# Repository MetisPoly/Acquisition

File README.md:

# Acquisition

Voici le _repository_ pour l'équipe d'acquisition des données. Vous trouverez ici les divers codes et schémas de PCB associés à l'équipe.

Si vous n'êtes pas familier avec l'utilisation de _GitHub_, référez-vous à la documentation suivante:
https://docs.google.com/document/d/1EO_ZASFU5IuZBYXzvok4T1j8fdGlCsaUoXh5eMMK4JE/edit?usp=sharing

Si vous voulez apporter des modifications au code existant dans ce _repo_, vous devez impérativement faire un _pull request_. 
Prenez également garde aux branches sur lesquelles vous développez.

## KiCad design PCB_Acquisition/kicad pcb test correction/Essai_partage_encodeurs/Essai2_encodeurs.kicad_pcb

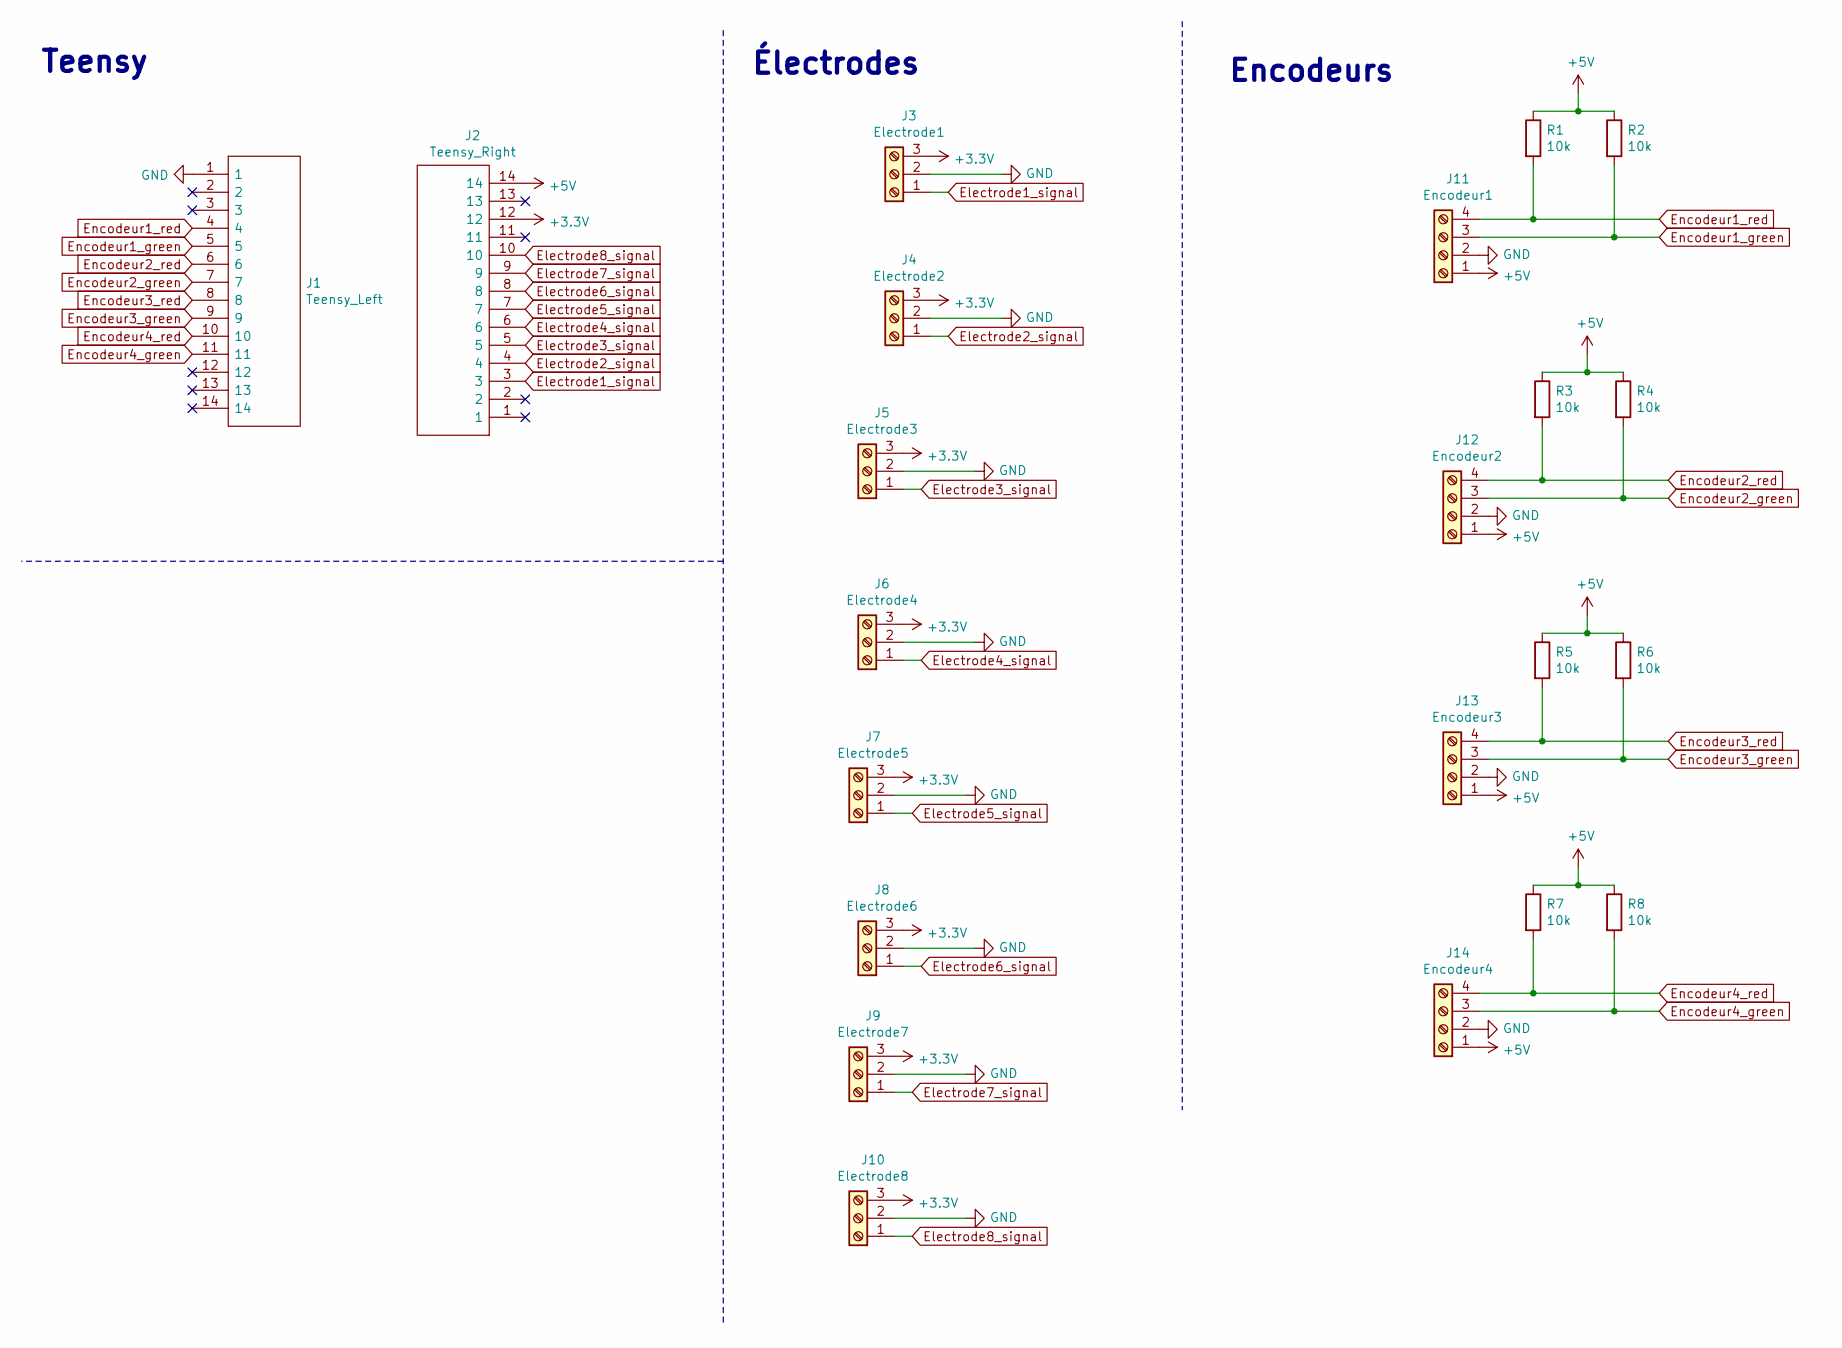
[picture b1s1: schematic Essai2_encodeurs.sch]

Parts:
J1: Teensy_Left; PinSocket_1x14_P2.54mm_Vertical
J2: Teensy_Right; PinSocket_1x14_P2.54mm_Vertical
J3: Electrode1; TerminalBlock_bornier-3_P5.08mm
J4: Electrode2; TerminalBlock_bornier-3_P5.08mm
J5: Electrode3; TerminalBlock_bornier-3_P5.08mm
J6: Electrode4; TerminalBlock_bornier-3_P5.08mm
J7: Electrode5; TerminalBlock_bornier-3_P5.08mm
J8: Electrode6; TerminalBlock_bornier-3_P5.08mm
J9: Electrode7; TerminalBlock_bornier-3_P5.08mm
J10: Electrode8; TerminalBlock_bornier-3_P5.08mm
J11: Encodeur1; TerminalBlock_bornier-4_P5.08mm
J12: Encodeur2; TerminalBlock_bornier-4_P5.08mm
J13: Encodeur3; TerminalBlock_bornier-4_P5.08mm
J14: Encodeur4; TerminalBlock_bornier-4_P5.08mm
R1, R2, R3, R4, R5, R6, R7, R8: 10k; R_0603_1608Metric

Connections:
+3V3: J2.12, J3.3, J4.3, J5.3, J6.3, J7.3, J8.3, J9.3, J10.3
+5V: J2.14, J11.1, J12.1, J13.1, J14.1, R1.1, R2.1, R3.1, R4.1, R5.1, R6.1, R7.1, R8.1
Electrode1_signal: J2.3, J3.1
Electrode2_signal: J2.4, J4.1
Electrode3_signal: J2.5, J5.1
Electrode4_signal: J2.6, J6.1
Electrode5_signal: J2.7, J7.1
Electrode6_signal: J2.8, J8.1
Electrode7_signal: J2.9, J9.1
Electrode8_signal: J2.10, J10.1
Encodeur1_green: J1.5, J11.3, R2.2
Encodeur1_red: J1.4, J11.4, R1.2
Encodeur2_green: J1.7, J12.3, R4.2
Encodeur2_red: J1.6, J12.4, R3.2
Encodeur3_green: J1.9, J13.3, R6.2
Encodeur3_red: J1.8, J13.4, R5.2
Encodeur4_green: J1.11, J14.3, R8.2
Encodeur4_red: J1.10, J14.4, R7.2
GND: J1.1, J3.2, J4.2, J5.2, J6.2, J7.2, J8.2, J9.2, J10.2, J11.2, J12.2, J13.2, J14.2

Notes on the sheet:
Teensy
Électrodes
Encodeurs

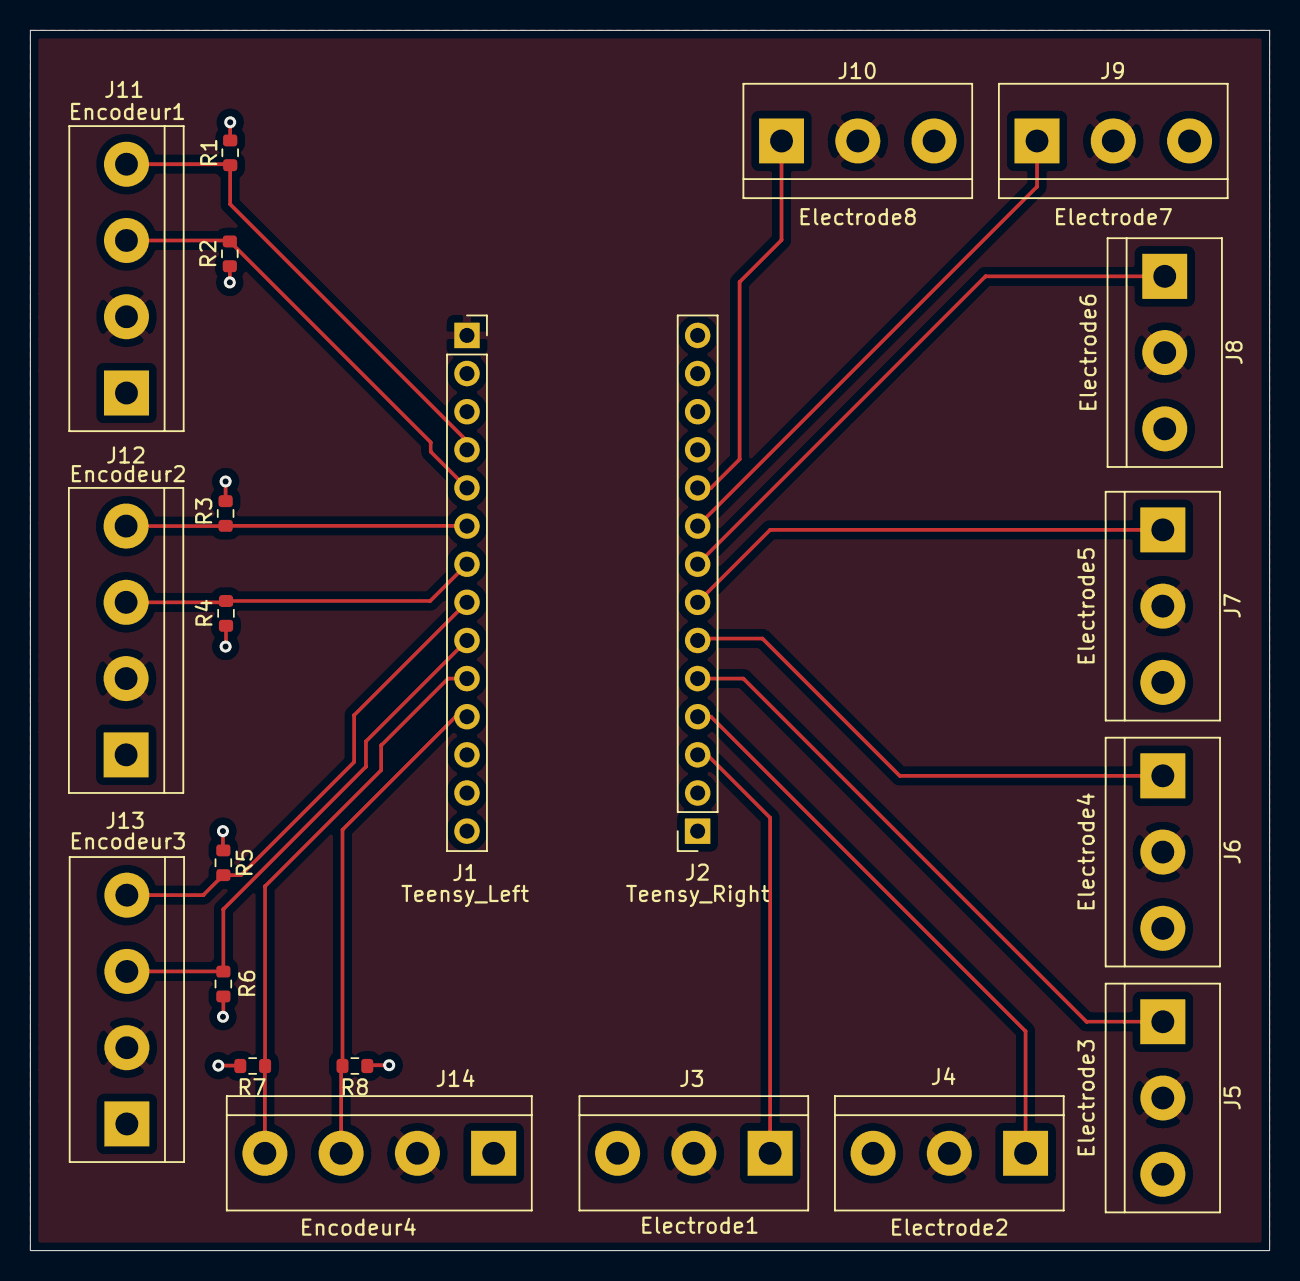
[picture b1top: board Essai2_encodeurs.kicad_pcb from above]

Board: 4 copper layers, 82.5 x 81.3 mm, 22 parts (0 on the bottom side), 19 nets.

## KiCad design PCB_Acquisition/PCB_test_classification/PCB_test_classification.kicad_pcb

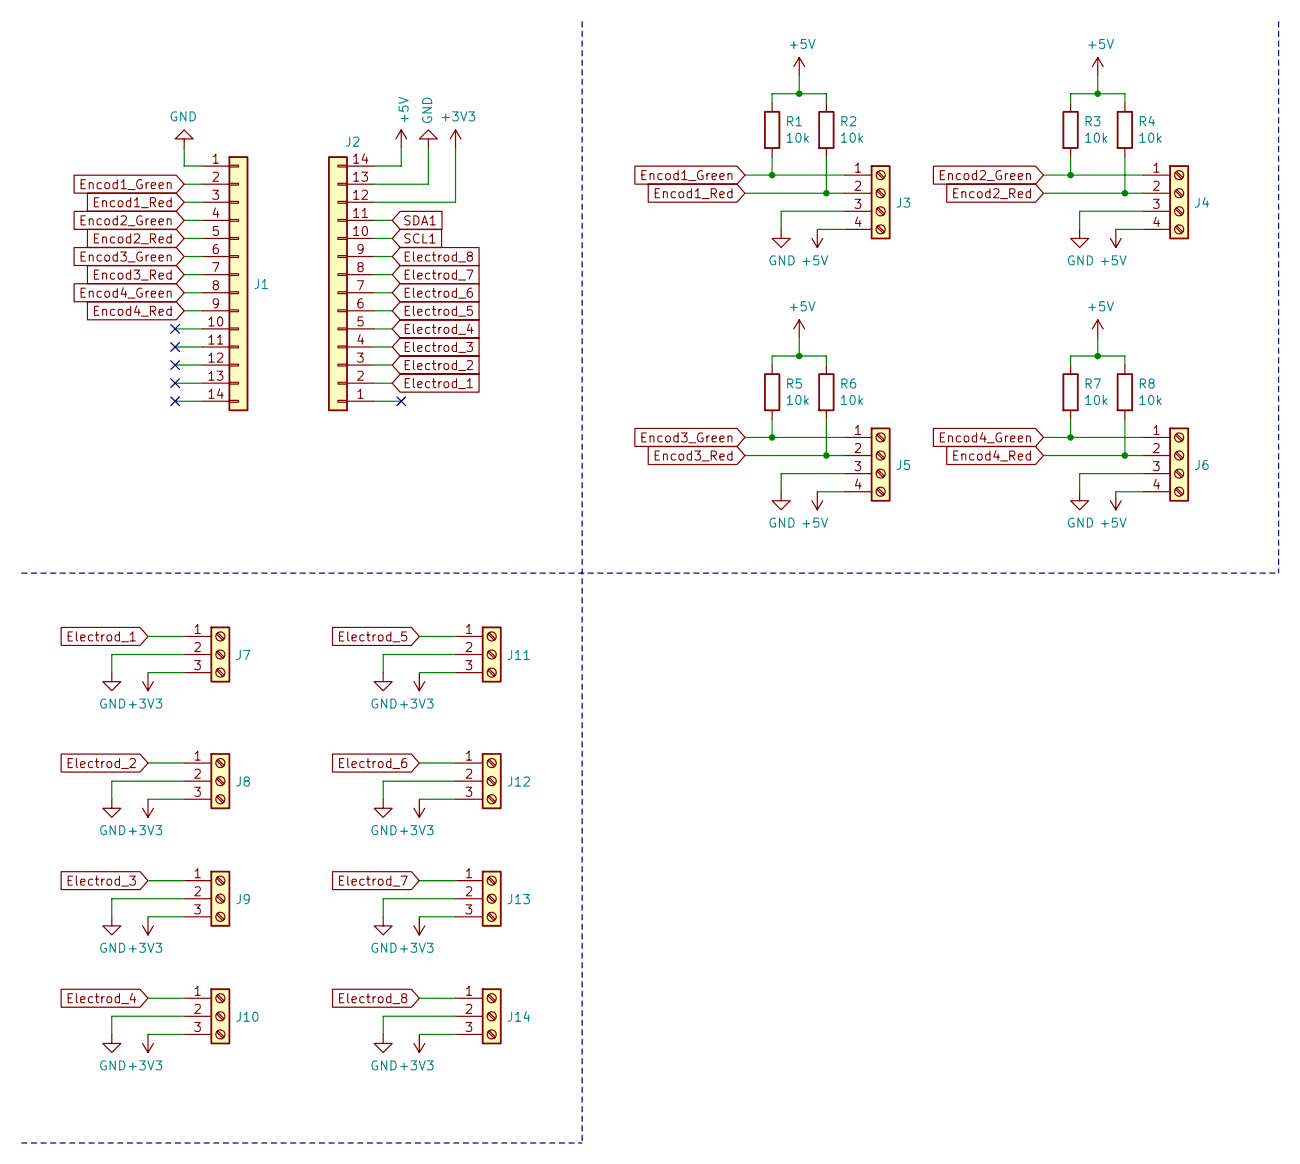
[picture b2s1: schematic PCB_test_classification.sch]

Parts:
J1, J2: Conn_01x14; PinSocket_1x14_P2.54mm_Vertical
J3, J4, J5, J6: Screw_Terminal_01x04; TerminalBlock_bornier-4_P5.08mm
J7, J8, J9, J10, J11, J12, J13, J14: Screw_Terminal_01x03; TerminalBlock_bornier-3_P5.08mm
R1, R2, R3, R4, R5, R6, R7, R8: 10k; R_0201_0603Metric

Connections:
+3V3: J2.12, J7.3, J8.3, J9.3, J10.3, J11.3, J12.3, J13.3, J14.3
+5V: J2.14, J3.4, J4.4, J5.4, J6.4, R1.1, R2.1, R3.1, R4.1, R5.1, R6.1, R7.1, R8.1
Electrod_1: J2.2, J7.1
Electrod_2: J2.3, J8.1
Electrod_3: J2.4, J9.1
Electrod_4: J2.5, J10.1
Electrod_5: J2.6, J11.1
Electrod_6: J2.7, J12.1
Electrod_7: J2.8, J13.1
Electrod_8: J2.9, J14.1
Encod1_Green: J1.2, J3.1, R1.2
Encod1_Red: J1.3, J3.2, R2.2
Encod2_Green: J1.4, J4.1, R3.2
Encod2_Red: J1.5, J4.2, R4.2
Encod3_Green: J1.6, J5.1, R5.2
Encod3_Red: J1.7, J5.2, R6.2
Encod4_Green: J1.8, J6.1, R7.2
Encod4_Red: J1.9, J6.2, R8.2
GND: J1.1, J2.13, J3.3, J4.3, J5.3, J6.3, J7.2, J8.2, J9.2, J10.2, J11.2, J12.2, J13.2, J14.2
SCL1: J2.10
SDA1: J2.11

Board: 4 copper layers, 22 parts (0 on the bottom side), 19 nets, no tracks yet.

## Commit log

2022-05-24 Transfer of acquisition files
2022-05-27 Test
2022-05-29 Clean up of h file
    Correction des noms de constantes pour être plus représentatives de ce qu'elles sont dans le programme. Correction pour atteindre les standards de code c++ au niveau du nom des variables.
2022-06-02 Bugfix-TestAlexandre
    Ceci est un test.
2022-06-02 Bugfix-TestAlexandre
2022-06-08 PCB exo travail
    Ajout des fichiers KiCAD pour le PCB de test pour l'équipe de classification
2022-06-08 PCB test classification
    PCB pour l'exo de travail de l'équipe classification
2022-06-09 Delete PCB_test_classification
    Wrong version of PCB
2022-06-09 Add PCB_test_classification
    Add right version of test PCB for Classification team
2022-06-11 Add bitwise operation files/ cleanup comments
2022-06-12 Test démo GitHub
    Ajout d'un commentaire pour la démo du test GitHub
2022-06-15 First commit with vscode for GUI
2022-06-17 Implementation pour 8 electrodes et 4 encodeurs
2022-06-18 Start and stop acquiring data implemented
2022-06-19 Implementation of npy file creation
2022-06-19 Added comments to all files
2022-06-19 Fixing sendData.h and plot values
2022-07-05 Commit for addition of GUI for classification team
2022-07-12 Ajout de paths relatifs pour créer des fichiers directement dans le dossier
2022-07-14 fixation include
    fixer les includes
